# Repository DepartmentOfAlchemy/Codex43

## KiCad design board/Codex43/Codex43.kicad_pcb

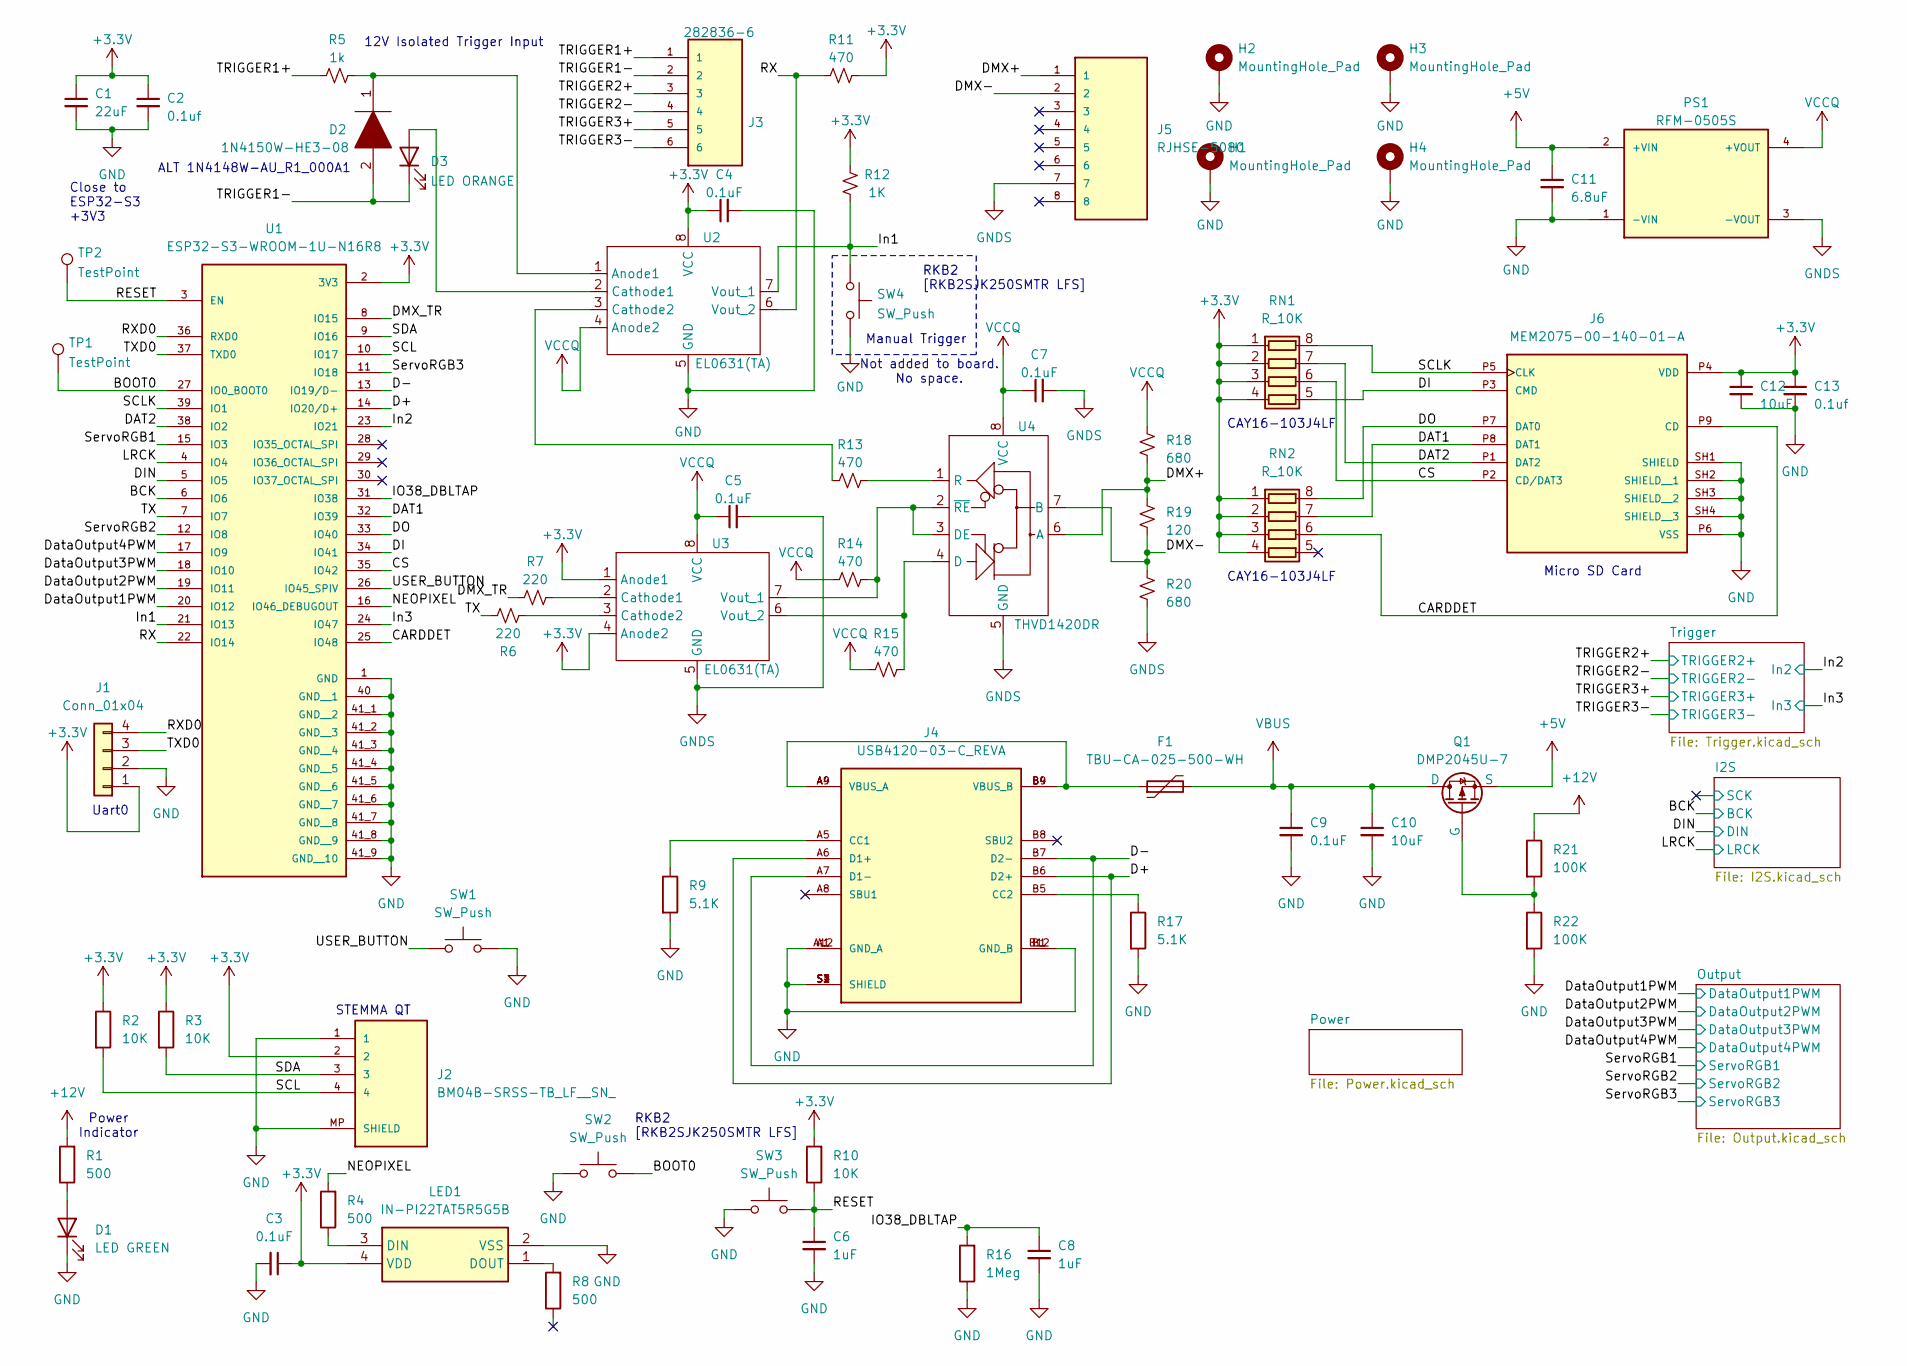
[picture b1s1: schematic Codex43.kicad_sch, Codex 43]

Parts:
C1: 22uF; C_0805_2012Metric
C2, C13: 0.1uf; C_0603_1608Metric
C3, C4, C5, C7, C9: 0.1uF; C_0603_1608Metric
C6, C8: 1uF; C_0603_1608Metric
C10, C12: 10uF; C_0805_2012Metric
C11: 6.8uF; C_0805_2012Metric
D1: LED GREEN; LED_0603_1608Metric
D2: 1N4150W-HE3-08; D_SOD-123; Manufacturer_Part_Number S1GTR
D3: LED ORANGE; LED_0603_1608Metric
F1: TBU-CA-025-500-WH; Fuse_Bourns_TBU-CA
H1, H2, H3, H4: MountingHole_Pad; MountingHole_3.2mm_M3_ISO7380_Pad_TopBottom
J1: Conn_01x04; PinHeader_1x04_P2.54mm_Vertical
J2: BM04B-SRSS-TB_LF__SN_; JST_SH_BM04B-SRSS-TB_1x04-1MP_P1.00mm_Vertical; PARTREV N/A
J3: 282836-6; TE_282836-6; PARTREV J1
J4: USB4120-03-C_REVA; GCT_USB4120-03-C_REVA; PARTREV A
J5: RJHSE-5080; AMPHENOL_RJHSE-5080; PARTREV G
J6: MEM2075-00-140-01-A; GCT_MEM2075-00-140-01-A; PARTREV A
LED1: IN-PI22TAT5R5G5B; INPI22TAT5R5G5B; Mouser Part Number 743-IN-PI22TAT5R5G5B
PS1: RFM-0505S; CONV_RFM-0505S; PARTREV 0
Q1: DMP2045U-7; SOT-23_DIO
R1, R4, R8: 500; R_0603_1608Metric
R2, R3, R10: 10K; R_0603_1608Metric
R5: 1k; R_0603_1608Metric
R6, R7: 220; R_0603_1608Metric
R9, R17: 5.1K; R_0603_1608Metric
R11, R13, R14, R15: 470; R_0603_1608Metric
R12: 1K; R_0603_1608Metric
R16: 1Meg; R_0603_1608Metric
R18, R20: 680; R_0603_1608Metric
R19: 120; R_0603_1608Metric
R21, R22: 100K; R_0603_1608Metric
RN1, RN2: R_10K; R_Array_Convex_4x0603
SW1, SW2, SW3, SW4: SW_Push; SW_Push_1P1T_NO_RKB2SJK250SMTR LFS
TP1, TP2: TestPoint; TestPoint_Pad_D2.5mm
U1: ESP32-S3-WROOM-1U-N16R8; XCVR_ESP32-S3-WROOM-1U-N16R8; PARTREV v1.1
U2, U3: EL0631(TA); EL0631(TA)-SOP-8_3.9x4.9mm_P1.27mm
U4: THVD1420DR; SOIC-8-TE_3.9x4.9mm_P1.27mm

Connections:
+3.3V: C1.1, C2.1, C3.1, C4.1, C12.1, C13.1, J1.1, J2.2, J6.P4 (VDD), LED1.4 (VDD), R2.1, R3.1, R10.2, R11.1, R12.2, RN1.1 (R1.1), RN1.2 (R2.1), RN1.3 (R3.1), RN1.4 (R4.1), RN2.1 (R1.1), RN2.2 (R2.1), RN2.3 (R3.1), RN2.4 (R4.1), U1.2 (3V3), U2.8 (VCC), U3.1 (Anode1), U3.4 (Anode2); also elsewhere on the board
+5V: C11.1, PS1.2 (+VIN), Q1.2 (S); also elsewhere on the board
+12V: R1.2, R21.1; also elsewhere on the board
/BCK: U1.6 (IO6); also elsewhere on the board
/BOOT0: SW2.2, TP1.1, U1.27 (IO0_BOOT0)
/CARDDET: J6.P9 (CD), RN2.6 (R3.2), U1.25 (IO48)
/CS: J6.P2 (CD/DAT3), RN1.6 (R3.2), U1.35 (IO42)
/D+: J4.A6 (D1+), J4.B6 (D2+), U1.14 (IO20/D+)
/D-: J4.A7 (D1-), J4.B7 (D2-), U1.13 (IO19/D-)
/DAT1: J6.P8 (DAT1), RN2.7 (R2.2), U1.32 (IO39)
/DAT2: J6.P1 (DAT2), RN1.7 (R2.2), U1.38 (IO2)
/DI: J6.P3 (CMD), RN1.5 (R4.2), U1.34 (IO41)
/DIN: U1.5 (IO5); also elsewhere on the board
/DMX+: J5.1, R18.2, R19.1, U4.6 (A)
/DMX-: J5.2, R19.2, R20.1, U4.7 (B)
/DMX_TR: R7.2, U1.8 (IO15)
/DO: J6.P7 (DAT0), RN2.8 (R1.2), U1.33 (IO40)
/DataOutput1PWM: U1.20 (IO12); also elsewhere on the board
/DataOutput2PWM: U1.19 (IO11); also elsewhere on the board
/DataOutput3PWM: U1.18 (IO10); also elsewhere on the board
/DataOutput4PWM: U1.17 (IO9); also elsewhere on the board
/IO38_DBLTAP: C8.1, R16.2, U1.31 (IO38)
/In1: R12.1, SW4.1, U1.21 (IO13), U2.7 (Vout_1)
/In2: U1.23 (IO21); also elsewhere on the board
/In3: U1.24 (IO47); also elsewhere on the board
/LRCK: U1.4 (IO4); also elsewhere on the board
/NEOPIXEL: R4.2, U1.16 (IO46_DEBUGOUT)
/RESET: C6.1, R10.1, SW3.2, TP2.1, U1.3 (EN)
/RX: R11.2, U1.22 (IO14), U2.6 (Vout_2)
/RXD0: J1.4, U1.36 (RXD0)
/SCL: J2.4, R2.2, U1.10 (IO17)
/SCLK: J6.P5 (CLK), RN1.8 (R1.2), U1.39 (IO1)
/SDA: J2.3, R3.2, U1.9 (IO16)
/ServoRGB1: U1.15 (IO3); also elsewhere on the board
/ServoRGB2: U1.12 (IO8); also elsewhere on the board
/ServoRGB3: U1.11 (IO18); also elsewhere on the board
/TRIGGER1+: J3.1, R5.2
/TRIGGER1-: D2.2, D3.1 (K), J3.2
/TRIGGER2+: J3.3; also elsewhere on the board
/TRIGGER2-: J3.4; also elsewhere on the board
/TRIGGER3+: J3.5; also elsewhere on the board
/TRIGGER3-: J3.6; also elsewhere on the board
/TX: R6.2, U1.7 (IO7)
/TXD0: J1.3, U1.37 (TXD0)
/USER_BUTTON: SW1.1, U1.26 (IO45_SPIV)
GND: C1.2, C2.2, C3.2, C4.2, C6.2, C8.2, C9.2, C10.2, C11.2, C12.2, C13.2, D1.1 (K), H1.1, H2.1, H3.1, H4.1, J1.2, J2.1, J2.MP (SHIELD), J4.A1 (GND_A), J4.A12 (GND_A), J4.B1 (GND_B), J4.B12 (GND_B), J4.S1 (SHIELD), J4.S2 (SHIELD), J4.S3 (SHIELD), J4.S4 (SHIELD), J6.P6 (VSS), J6.SH1 (SHIELD), J6.SH2 (SHIELD__1), J6.SH3 (SHIELD__2), J6.SH4 (SHIELD__3), LED1.2 (VSS), PS1.1 (-VIN), R9.2, R16.1, R17.2, R22.2, SW1.2, SW2.1, SW3.1, SW4.2, U1.1 (GND), U1.40 (GND__1), U1.41_1 (GND__2), U1.41_2 (GND__3), U1.41_3 (GND__4), U1.41_4 (GND__5), U1.41_5 (GND__6), U1.41_6 (GND__7), U1.41_7 (GND__8), U1.41_8 (GND__9), U1.41_9 (GND__10), U2.5 (GND); also elsewhere on the board
GNDS: C5.2, C7.2, J5.7, PS1.3 (-VOUT), R20.2, U3.5 (GND), U4.5 (GND)
unnamed: D1.2 (A), R1.1
unnamed: D3.2 (A), U2.2 (Cathode1)
unnamed: F1.1, J4.A4 (VBUS_A), J4.A9 (VBUS_A), J4.B4 (VBUS_B), J4.B9 (VBUS_B)
unnamed: J4.A5 (CC1), R9.1
unnamed: J4.B5 (CC2), R17.1
unnamed: LED1.3 (DIN), R4.1
unnamed: LED1.1 (DOUT), R8.2
unnamed: Q1.1 (G), R21.2, R22.1
unnamed: D2.1, R5.1, U2.1 (Anode1)
unnamed: R13.2, U2.3 (Cathode2)
unnamed: R7.1, U3.2 (Cathode1)
unnamed: R6.1, U3.3 (Cathode2)
unnamed: R14.1, U3.7 (Vout_1), U4.2 (~RE), U4.3 (DE)
unnamed: R15.1, U3.6 (Vout_2), U4.4 (D)
unnamed: R13.1, U4.1 (R)
VBUS: C9.1, C10.1, F1.3, Q1.3 (D)
VCCQ: C5.1, C7.1, PS1.4 (+VOUT), R14.2, R15.2, R18.1, U2.4 (Anode2), U3.8 (VCC), U4.8 (VCC)

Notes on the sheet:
RKB2 [RKB2SJK250SMTR LFS]
CAY16-103J4LF
Manual Trigger
Micro SD Card
Not added to board. No space.
Power Indicator
Close to ESP32-S3 +3V3
STEMMA QT
12V Isolated Trigger Input
ALT 1N4148W-AU_R1_000A1
Uart0

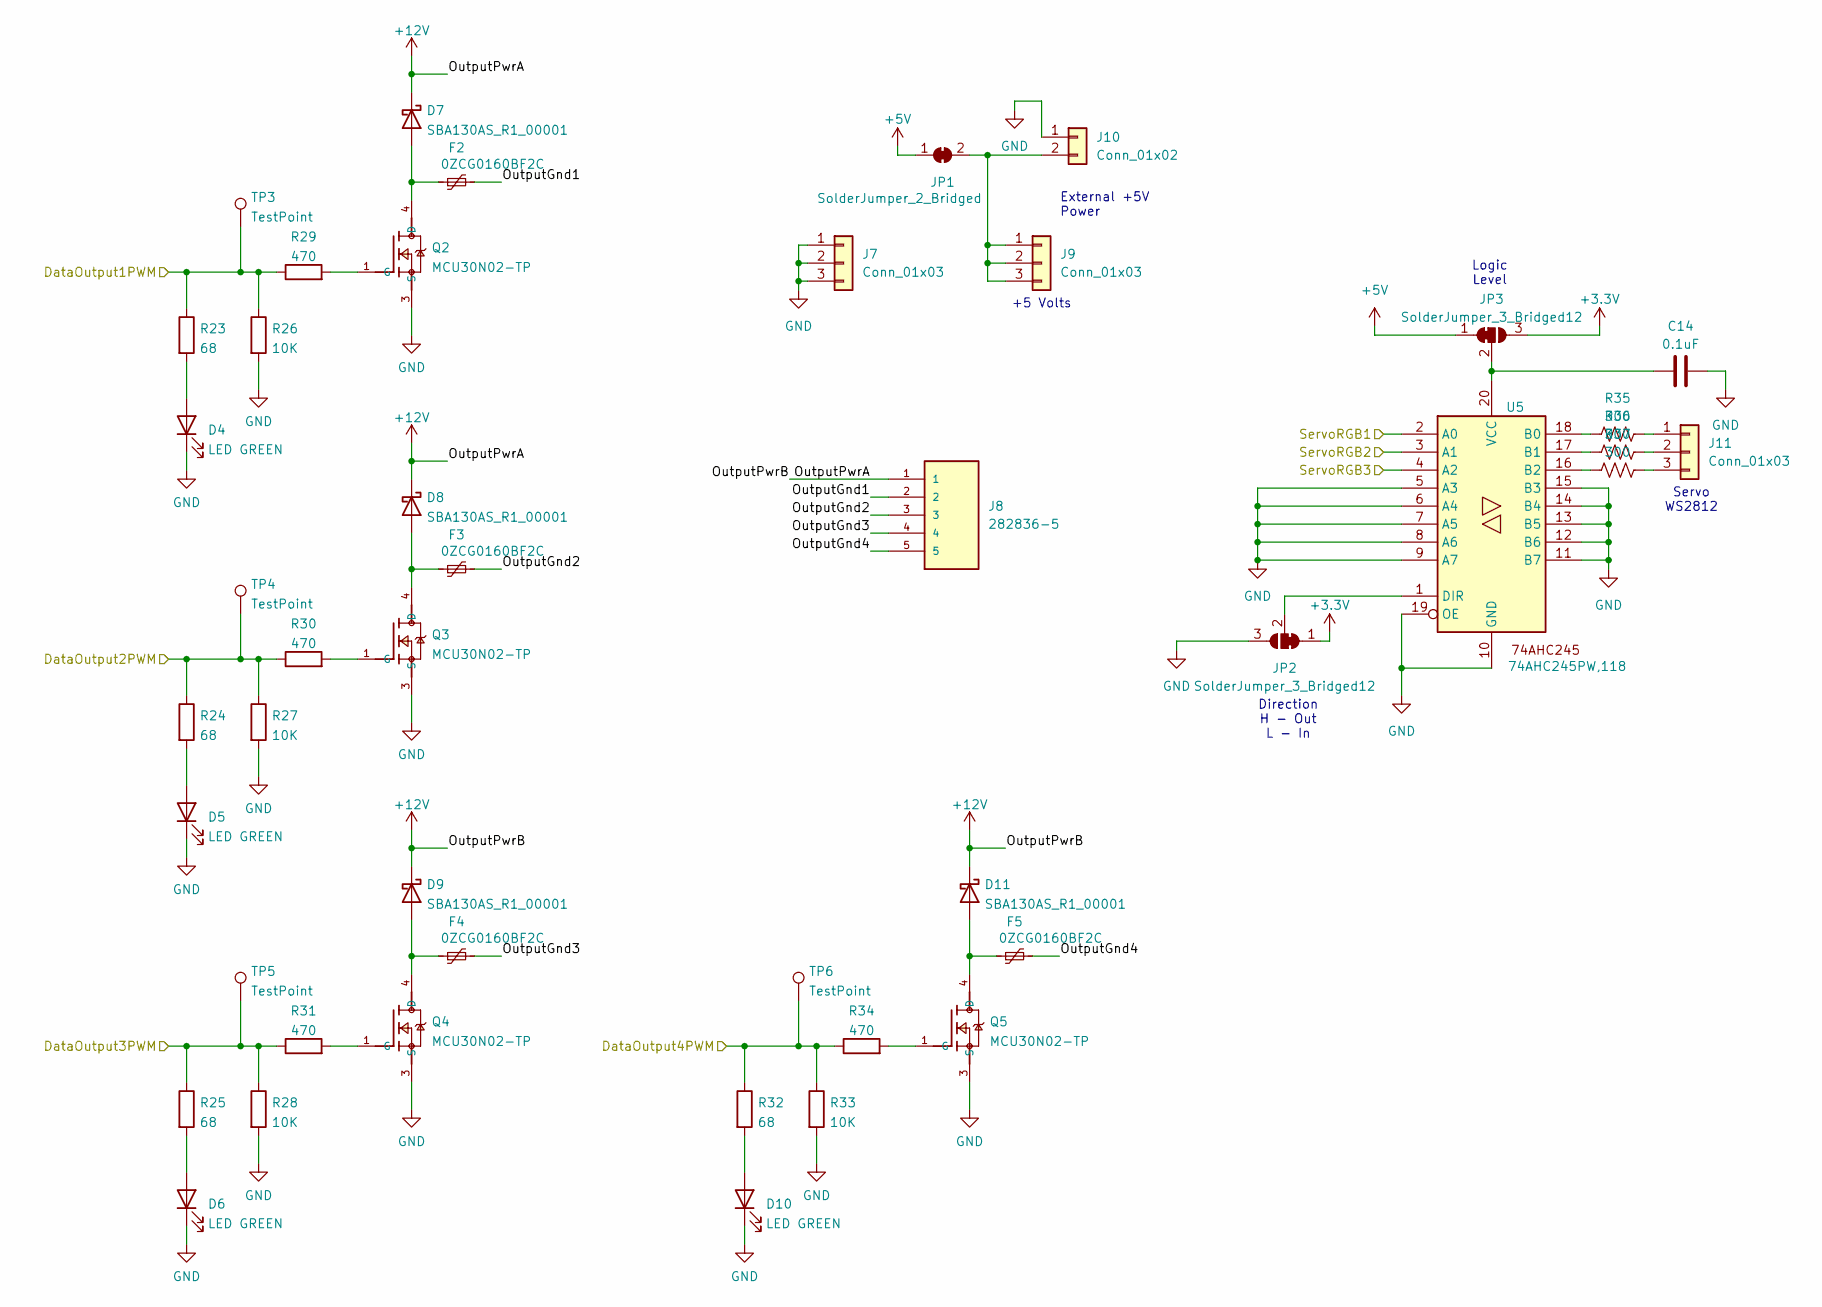
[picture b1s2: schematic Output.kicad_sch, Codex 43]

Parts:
C14: 0.1uF; C_0805_2012Metric_Pad1.18x1.45mm_HandSolder
D4, D5, D6, D10: LED GREEN; LED_0603_1608Metric
D7, D8, D9, D11: SBA130AS_R1_00001; D_SOD-123
F2, F3, F4, F5: 0ZCG0160BF2C; Fuse_1812_4532Metric
J7, J9, J11: Conn_01x03; PinHeader_1x03_P2.54mm_Vertical
J8: 282836-5; TE_282836-5; PARTREV J1
J10: Conn_01x02; PinHeader_1x02_P2.54mm_Vertical
JP1: SolderJumper_2_Bridged; SolderJumper-2_P1.3mm_Bridged_Pad1.0x1.5mm
JP2, JP3: SolderJumper_3_Bridged12; SolderJumper-3_P1.3mm_Bridged12_Pad1.0x1.5mm
Q2, Q3, Q4, Q5: MCU30N02-TP; TO229P991X239-3N
R23, R24, R25, R32: 68; R_0603_1608Metric
R26, R27, R28, R33: 10K; R_0603_1608Metric
R29, R30, R31, R34: 470; R_0603_1608Metric
R35, R36, R37: 300; R_0603_1608Metric
TP3, TP4, TP5, TP6: TestPoint; TestPoint_Pad_D2.5mm
U5: 74AHC245PW,118; SOP65P640X120-20N

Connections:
+3.3V: JP2.1 (A), JP3.3 (B); also elsewhere on the board
+5V: JP1.1 (A), JP3.1 (A); also elsewhere on the board
+12V: D7.1 (K), D8.1 (K), D9.1 (K), D11.1 (K), J8.1; also elsewhere on the board
/DataOutput1PWM: R23.1, R26.1, R29.1, TP3.1; also elsewhere on the board
/DataOutput2PWM: R24.1, R27.1, R30.1, TP4.1; also elsewhere on the board
/DataOutput3PWM: R25.1, R28.1, R31.1, TP5.1; also elsewhere on the board
/DataOutput4PWM: R32.1, R33.1, R34.1, TP6.1; also elsewhere on the board
/Output/OutputGnd1: F2.2, J8.2
/Output/OutputGnd2: F3.2, J8.3
/Output/OutputGnd3: F4.2, J8.4
/Output/OutputGnd4: F5.2, J8.5
/ServoRGB1: U5.2 (A0); also elsewhere on the board
/ServoRGB2: U5.3 (A1); also elsewhere on the board
/ServoRGB3: U5.4 (A2); also elsewhere on the board
GND: C14.2, D4.1 (K), D5.1 (K), D6.1 (K), D10.1 (K), J7.1, J7.2, J7.3, J10.1, JP2.3 (B), Q2.3 (S), Q3.3 (S), Q4.3 (S), Q5.3 (S), R26.2, R27.2, R28.2, R33.2, U5.5 (A3), U5.6 (A4), U5.7 (A5), U5.8 (A6), U5.9 (A7), U5.10 (GND), U5.11 (B7), U5.12 (B6), U5.13 (B5), U5.14 (B4), U5.15 (B3), U5.19 (OE); also elsewhere on the board
unnamed: D4.2 (A), R23.2
unnamed: D5.2 (A), R24.2
unnamed: D6.2 (A), R25.2
unnamed: D7.2 (A), F2.1, Q2.4 (D)
unnamed: D8.2 (A), F3.1, Q3.4 (D)
unnamed: D9.2 (A), F4.1, Q4.4 (D)
unnamed: D10.2 (A), R32.2
unnamed: D11.2 (A), F5.1, Q5.4 (D)
unnamed: J9.1, J9.2, J9.3, J10.2, JP1.2 (B)
unnamed: J11.1, R35.2
unnamed: J11.2, R36.2
unnamed: J11.3, R37.2
unnamed: JP2.2 (C), U5.1 (DIR)
unnamed: C14.1, JP3.2 (C), U5.20 (VCC)
unnamed: Q2.1 (G), R29.2
unnamed: Q3.1 (G), R30.2
unnamed: Q4.1 (G), R31.2
unnamed: Q5.1 (G), R34.2
unnamed: R35.1, U5.18 (B0)
unnamed: R36.1, U5.17 (B1)
unnamed: R37.1, U5.16 (B2)

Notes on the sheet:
+5 Volts
External +5V Power
Direction H - Out L - In
Servo WS2812
Logic Level

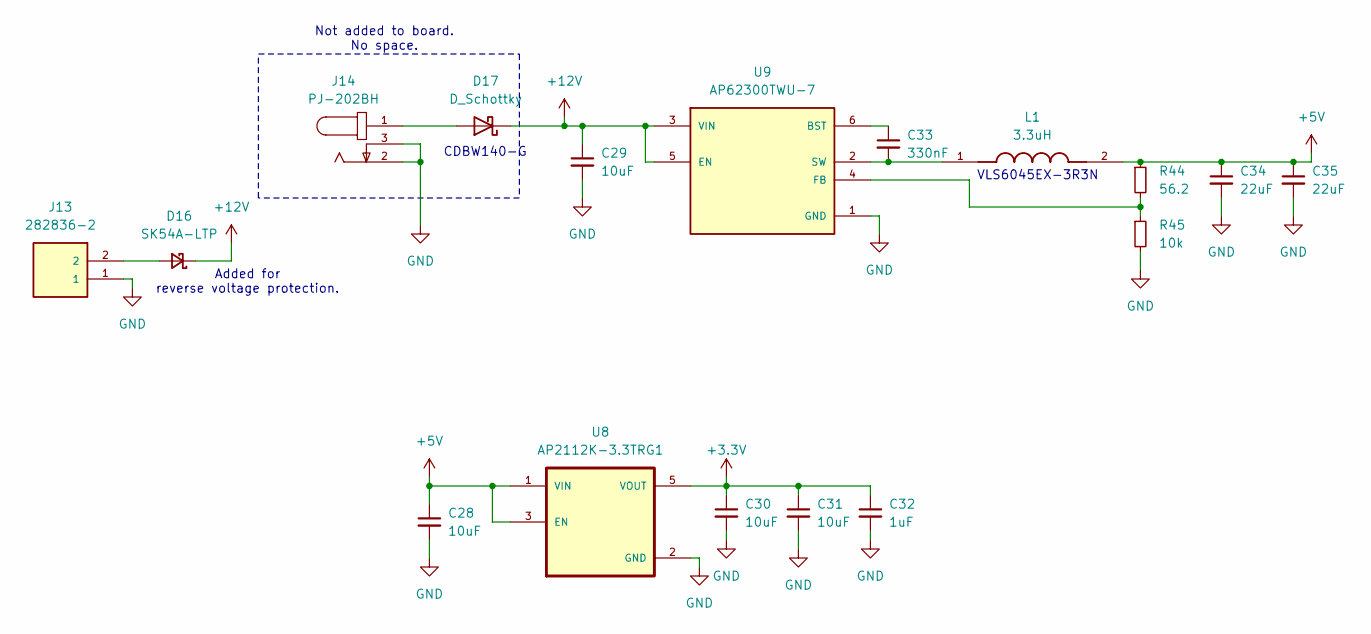
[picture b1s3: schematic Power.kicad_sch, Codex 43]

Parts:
C28, C29, C30, C31: 10uF; C_0805_2012Metric
C32: 1uF; C_0603_1608Metric
C33: 330nF; C_0603_1608Metric
C34, C35: 22uF; C_0805_2012Metric
D16: SK54A-LTP; D_SMA Modified
D17: D_Schottky; D_SOD-123
J13: 282836-2; TE_282836-2; PARTREV J1
J14: PJ-202BH; CUI_PJ-202BH; PART_REV 1.02
L1: 3.3uH; VLS6045EX-3R3N; PARTREV N/A
R44: 56.2; R_0603_1608Metric
R45: 10k; R_0603_1608Metric
U8: AP2112K-3.3TRG1; SOT95P285X140-5N; PARTREV 2-2
U9: AP62300TWU-7; SOT95P280X100-6N; PARTREV Rev. 3 - 2

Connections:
+3.3V: C30.1, C31.1, C32.1, U8.5 (VOUT); also elsewhere on the board
+5V: C28.1, C34.1, C35.1, L1.2, R44.1, U8.1 (VIN), U8.3 (EN); also elsewhere on the board
+12V: C29.1, D16.1 (K), D17.1 (K), U9.3 (VIN), U9.5 (EN); also elsewhere on the board
GND: C28.2, C29.2, C30.2, C31.2, C32.2, C34.2, C35.2, J13.1, J14.2, J14.3, R45.2, U8.2 (GND), U9.1 (GND); also elsewhere on the board
unnamed: D16.2 (A), J13.2
unnamed: D17.2 (A), J14.1
unnamed: C33.1, U9.6 (BST)
unnamed: R44.2, R45.1, U9.4 (FB)
unnamed: C33.2, L1.1, U9.2 (SW)

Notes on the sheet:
VLS6045EX-3R3N
Added for reverse voltage protection.
Not added to board. No space.
CDBW140-G

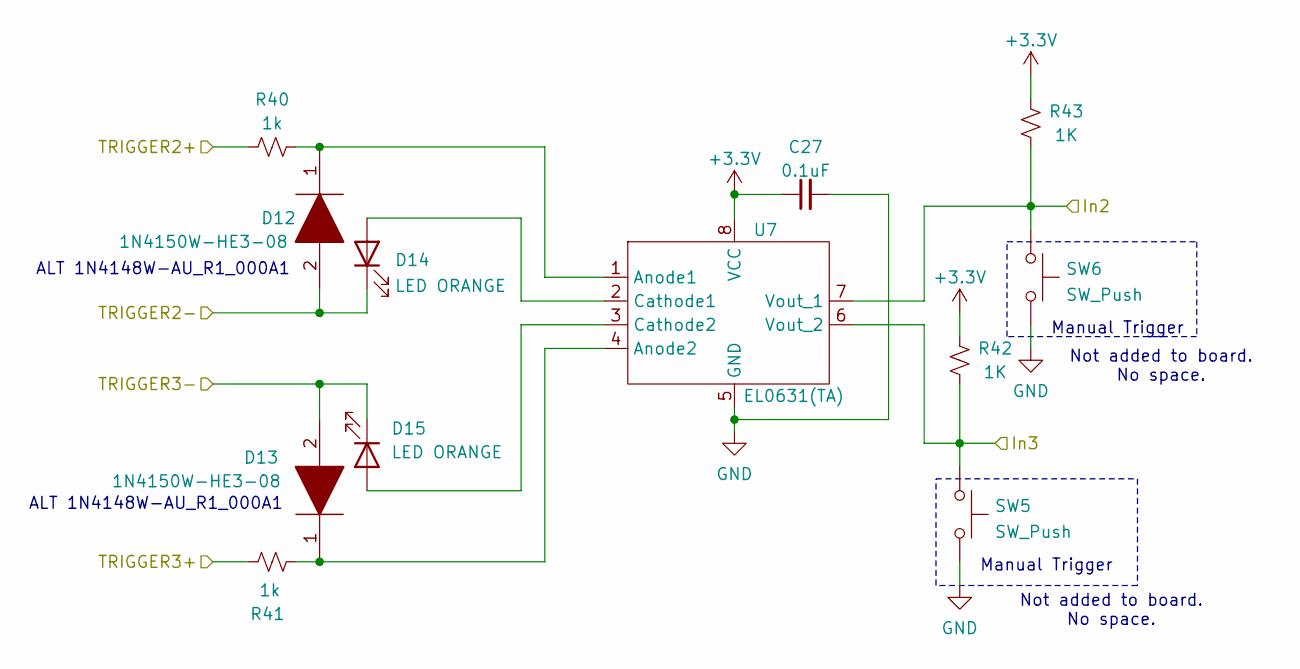
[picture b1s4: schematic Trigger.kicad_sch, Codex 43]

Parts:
C27: 0.1uF; C_0603_1608Metric
D12, D13: 1N4150W-HE3-08; D_SOD-123; Manufacturer_Part_Number S1GTR
D14, D15: LED ORANGE; LED_0603_1608Metric
R40, R41: 1k; R_0603_1608Metric
R42, R43: 1K; R_0603_1608Metric
SW5, SW6: SW_Push; SW_Push_1P1T_NO_RKB2SJK250SMTR LFS
U7: EL0631(TA); EL0631(TA)-SOP-8_3.9x4.9mm_P1.27mm

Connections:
+3.3V: C27.1, R42.2, R43.2, U7.8 (VCC); also elsewhere on the board
/In2: R43.1, SW6.1, U7.7 (Vout_1); also elsewhere on the board
/In3: R42.1, SW5.1, U7.6 (Vout_2); also elsewhere on the board
/TRIGGER2+: R40.2; also elsewhere on the board
/TRIGGER2-: D12.2, D14.1 (K); also elsewhere on the board
/TRIGGER3+: R41.2; also elsewhere on the board
/TRIGGER3-: D13.2, D15.1 (K); also elsewhere on the board
GND: C27.2, SW5.2, SW6.2, U7.5 (GND); also elsewhere on the board
unnamed: D14.2 (A), U7.2 (Cathode1)
unnamed: D15.2 (A), U7.3 (Cathode2)
unnamed: D12.1, R40.1, U7.1 (Anode1)
unnamed: D13.1, R41.1, U7.4 (Anode2)

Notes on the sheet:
ALT 1N4148W-AU_R1_000A1
Not added to board. No space.
Manual Trigger

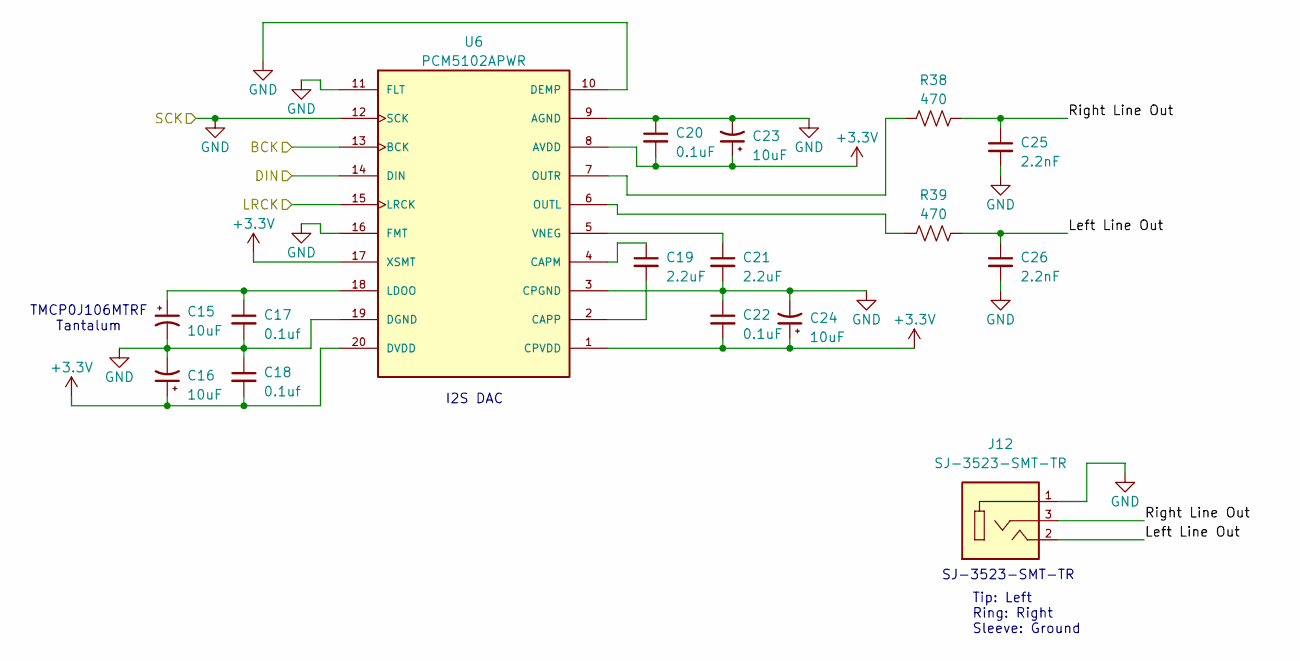
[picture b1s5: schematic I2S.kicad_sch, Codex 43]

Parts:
C15, C16, C23, C24: 10uF; CAPPM2012X120N
C17, C18: 0.1uf; C_0603_1608Metric
C19, C21: 2.2uF; C_0603_1608Metric
C20, C22: 0.1uF; C_0603_1608Metric
C25, C26: 2.2nF; C_0603_1608Metric
J12: SJ-3523-SMT-TR; CUI_SJ-3523-SMT-TR
R38, R39: 470; R_0603_1608Metric
U6: PCM5102APWR; SOP65P640X120-20N; PARTREV C

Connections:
+3.3V: C16.1, C18.2, C20.2, C22.2, C23.1, C24.1, U6.1 (CPVDD), U6.8 (AVDD), U6.17 (XSMT), U6.20 (DVDD); also elsewhere on the board
/BCK: U6.13 (BCK); also elsewhere on the board
/DIN: U6.14 (DIN); also elsewhere on the board
/I2S/Left Line Out: C26.1, J12.2, R39.2
/I2S/Right Line Out: C25.1, J12.3, R38.2
/LRCK: U6.15 (LRCK); also elsewhere on the board
GND: C15.2, C16.2, C17.2, C18.1, C20.1, C21.2, C22.1, C23.2, C24.2, C25.2, C26.2, J12.1, U6.3 (CPGND), U6.9 (AGND), U6.10 (DEMP), U6.11 (FLT), U6.12 (SCK), U6.16 (FMT), U6.19 (DGND); also elsewhere on the board
unnamed: C19.1, U6.4 (CAPM)
unnamed: C19.2, U6.2 (CAPP)
unnamed: C15.1, C17.1, U6.18 (LDOO)
unnamed: R39.1, U6.6 (OUTL)
unnamed: R38.1, U6.7 (OUTR)
unnamed: C21.1, U6.5 (VNEG)

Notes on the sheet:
Tip: Left Ring: Right Sleeve: Ground
SJ-3523-SMT-TR
I2S DAC
TMCP0J106MTRF Tantalum

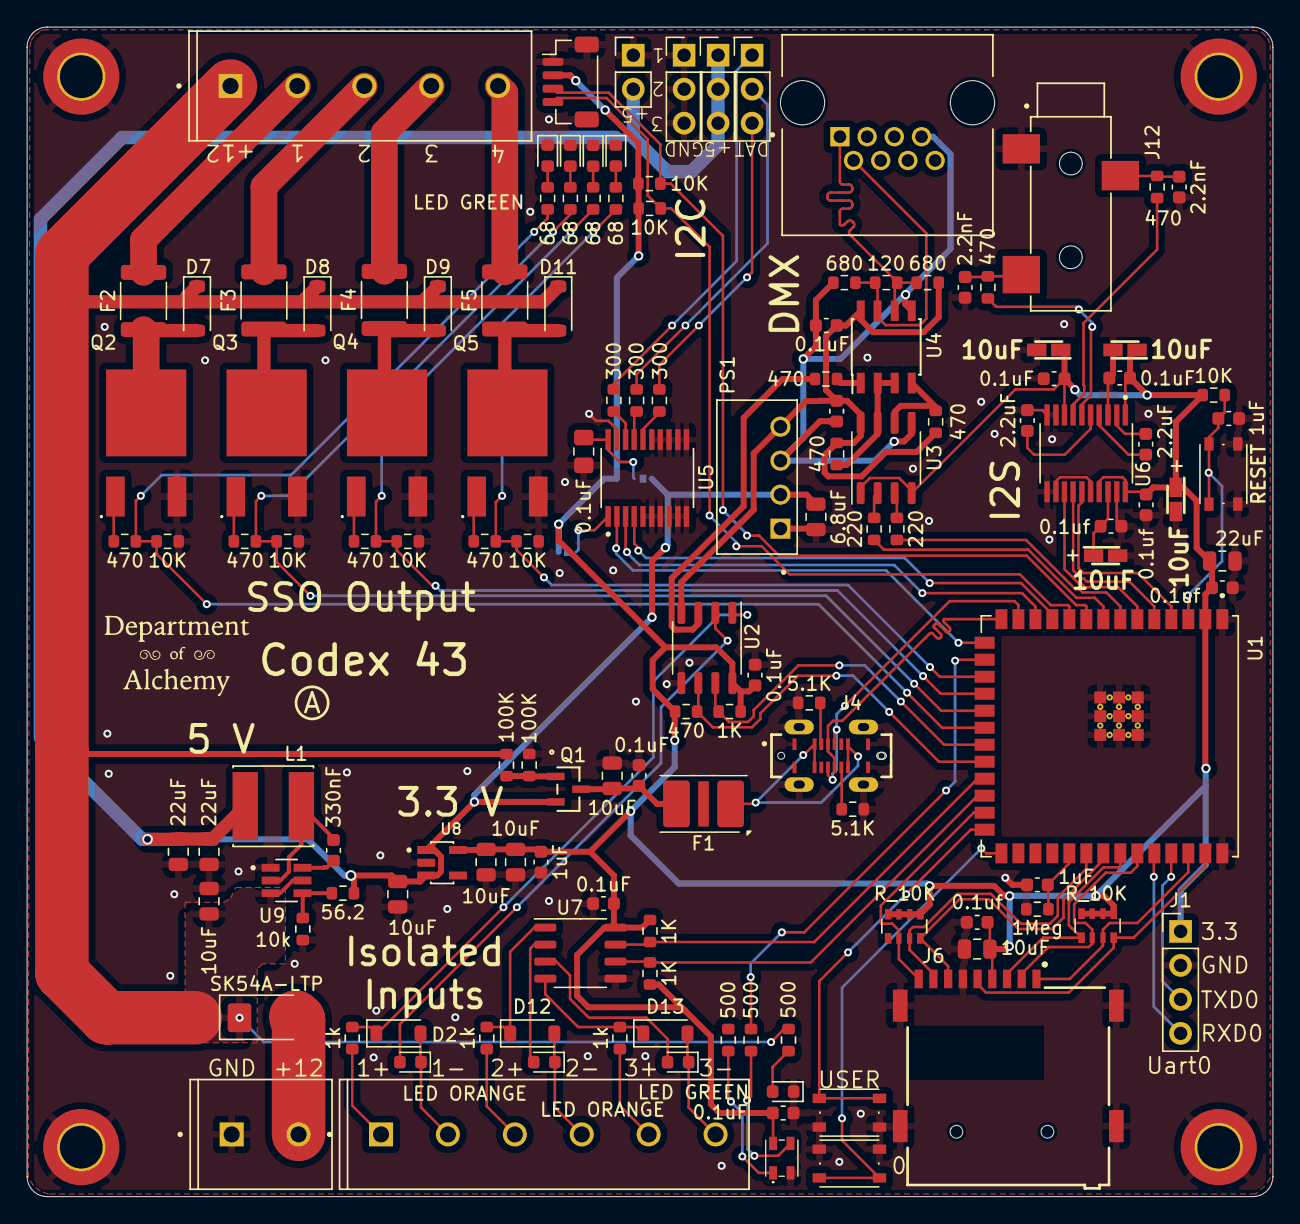
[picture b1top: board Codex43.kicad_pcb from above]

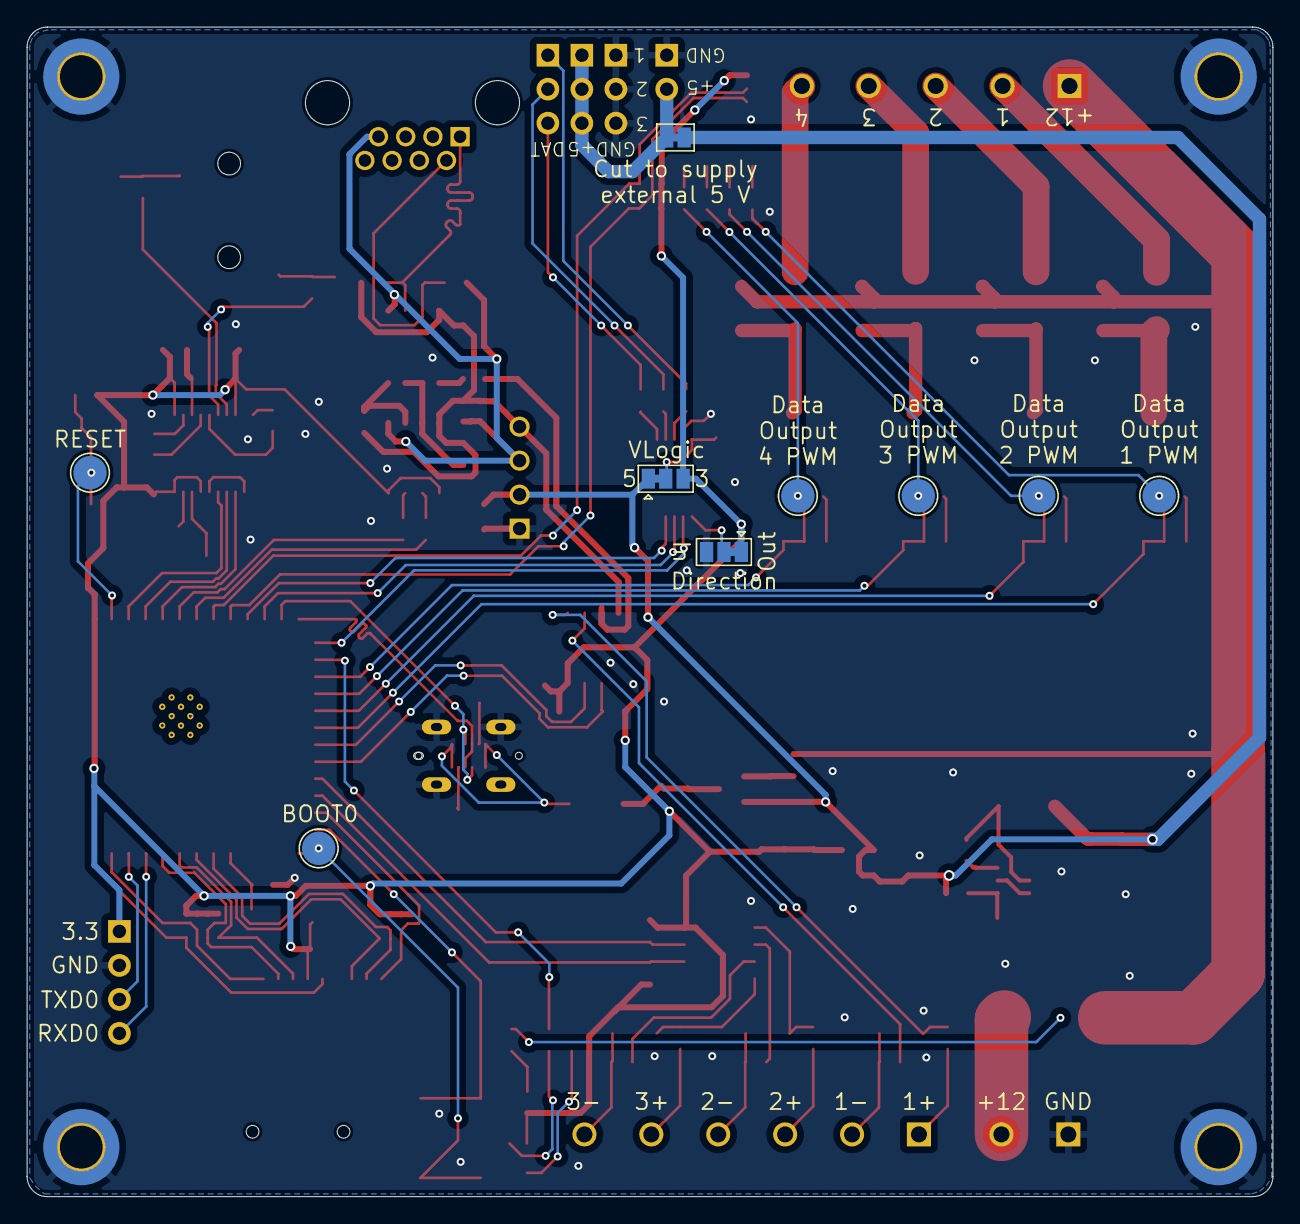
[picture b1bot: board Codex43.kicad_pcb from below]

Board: 2 copper layers, 93.1 x 87.4 mm, 149 parts (9 on the bottom side), 105 nets.

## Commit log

2024-08-17 Initial commit of Rev A board.
